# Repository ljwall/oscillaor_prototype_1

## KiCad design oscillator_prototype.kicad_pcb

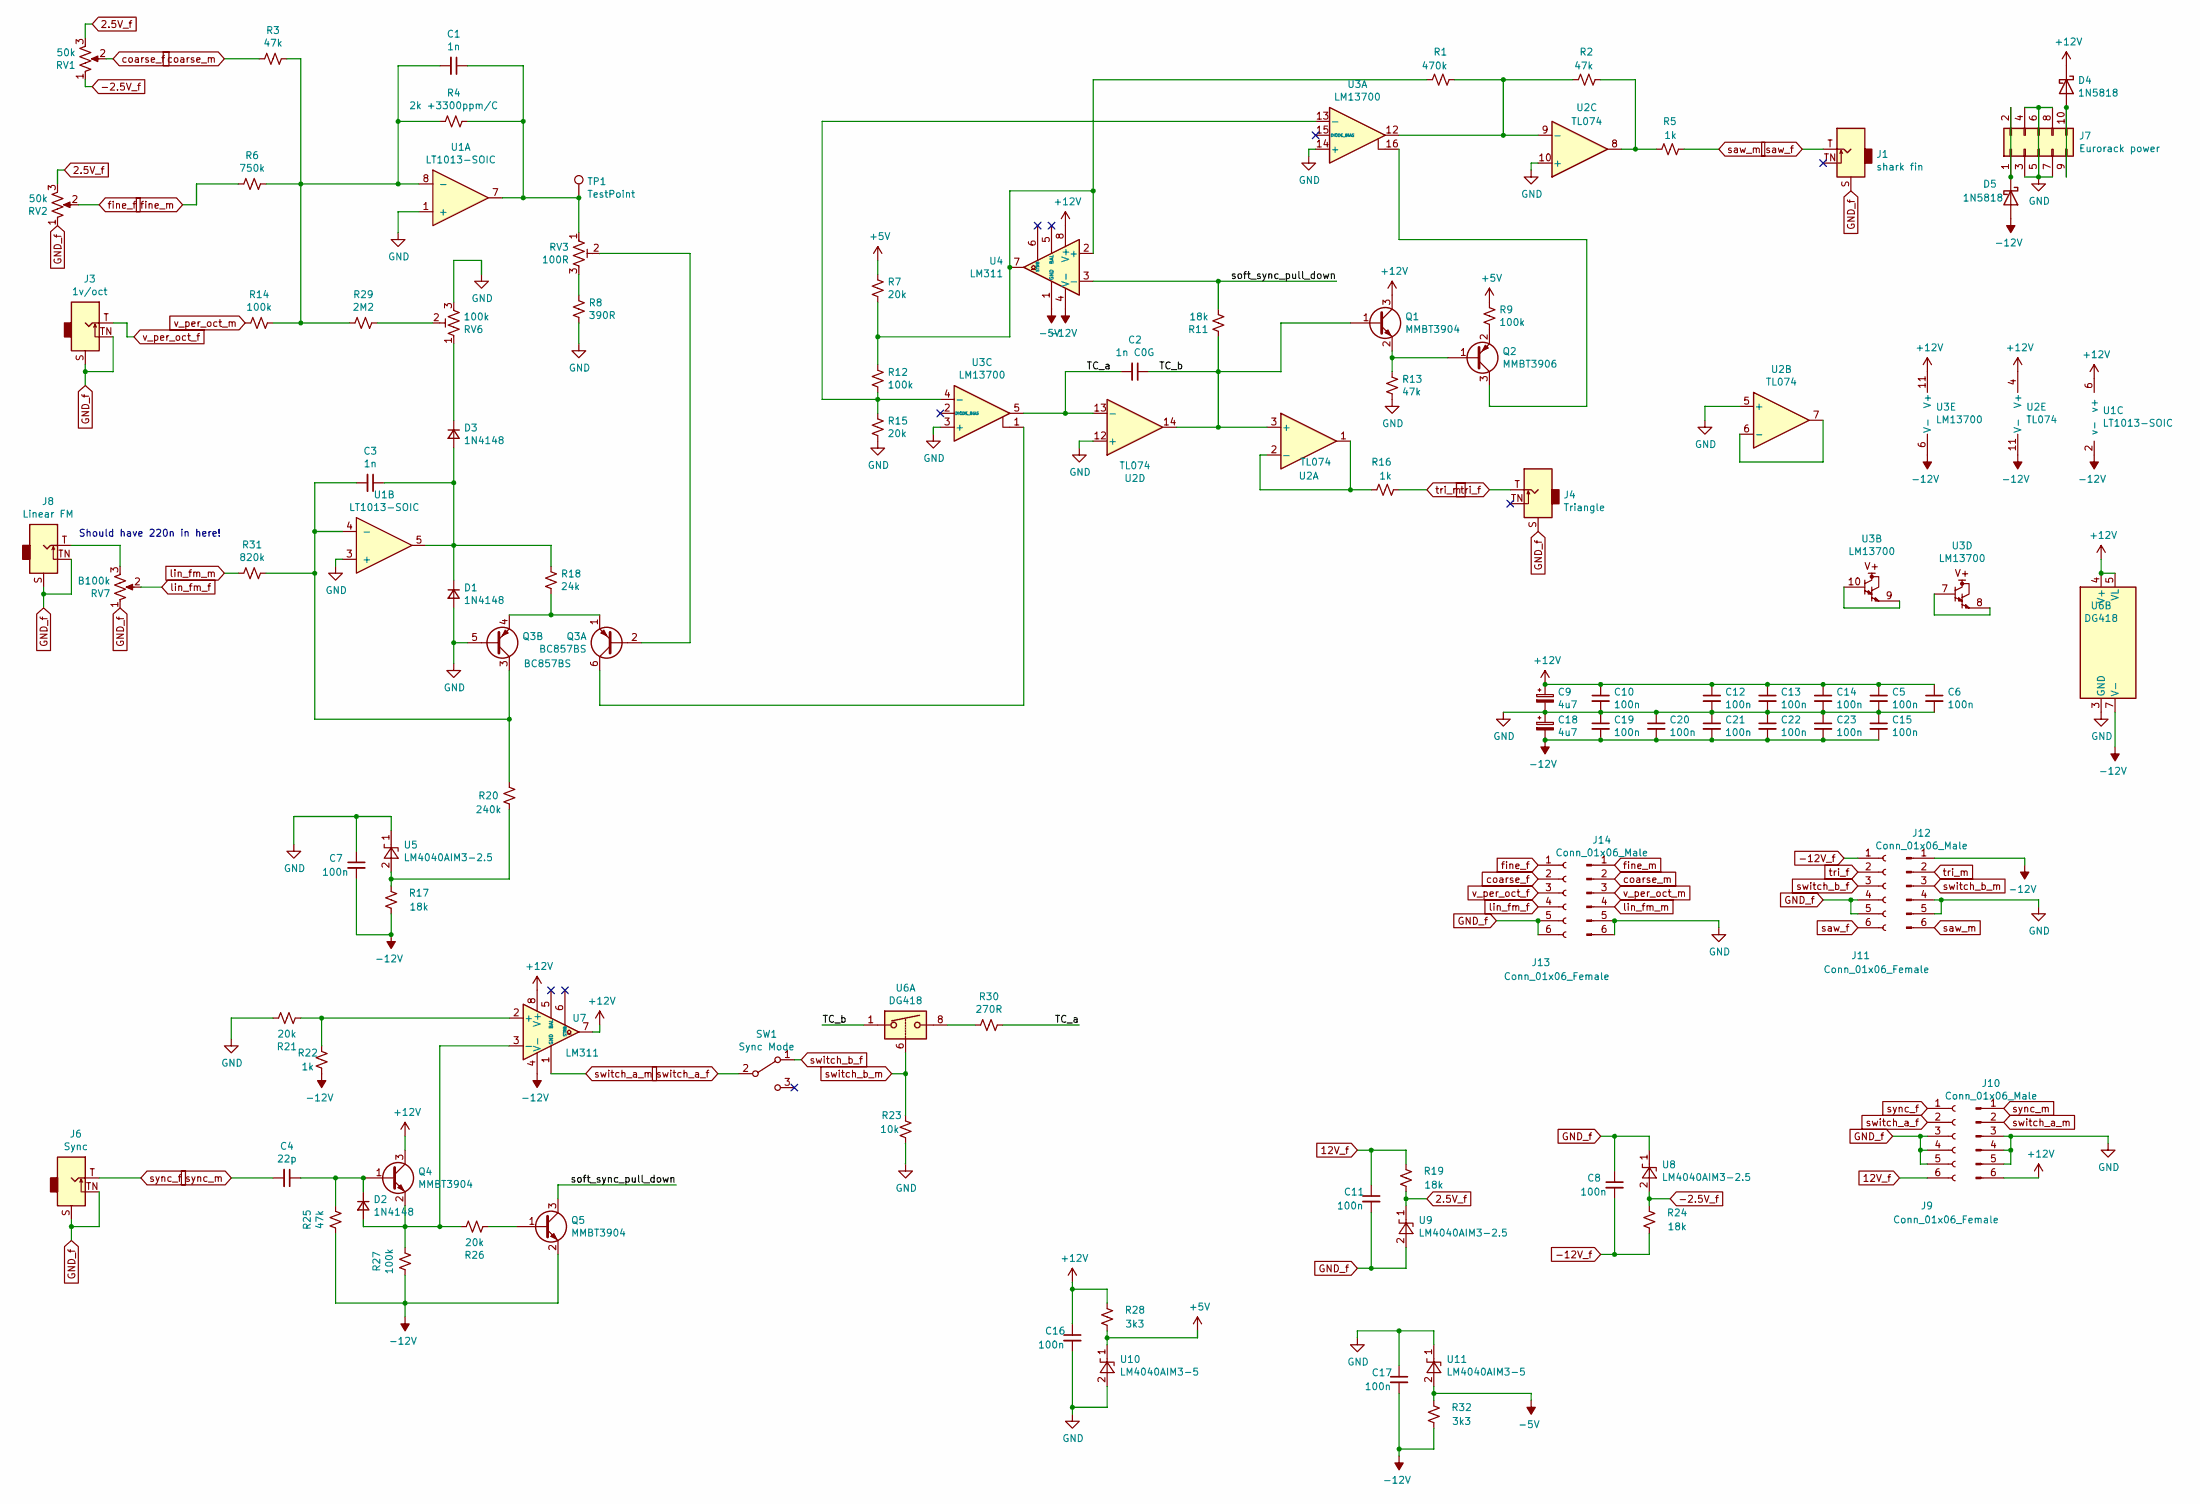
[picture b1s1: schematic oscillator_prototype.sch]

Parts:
C1, C3: 1n; C_0805_2012Metric_Pad1.18x1.45mm_HandSolder
C2: 1n C0G; C_0805_2012Metric_Pad1.18x1.45mm_HandSolder
C4: 22p; C_0805_2012Metric_Pad1.18x1.45mm_HandSolder
C5, C6, C7, C8, C10, C11, C12, C13, C14, C15, C16, C17, C19, C20, C21, C22, C23: 100n; C_0805_2012Metric_Pad1.18x1.45mm_HandSolder
C9, C18: 4u7; CP_Radial_D5.0mm_P2.00mm
D1, D2, D3: 1N4148; D_0805_2012Metric_Pad1.15x1.40mm_HandSolder
D4, D5: 1N5818; D_DO-41_SOD81_P10.16mm_Horizontal
J1: shark fin; Jack_3.5mm_QingPu_WQP-PJ398SM_Vertical_CircularHoles-transl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
J3: 1v/oct; Jack_3.5mm_QingPu_WQP-PJ398SM_Vertical_CircularHoles-transl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
J4: Triangle; Jack_3.5mm_QingPu_WQP-PJ398SM_Vertical_CircularHoles-transl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
J6: Sync; Jack_3.5mm_QingPu_WQP-PJ398SM_Vertical_CircularHoles-transl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
J7: Eurorack power; IDC-Header_2x05_P2.54mm_Horizontal
J8: Linear FM; Jack_3.5mm_QingPu_WQP-PJ398SM_Vertical_CircularHoles-transl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
J9, J11, J13: Conn_01x06_Female; PinHeader_1x06_P2.54mm_Vertical
J10, J12, J14: Conn_01x06_Male; PinHeader_1x06_P2.54mm_Vertical
Q1, Q4, Q5: MMBT3904; SOT-23
Q2: MMBT3906; SOT-23
Q3: BC857BS; SOT-363_SC-70-6
R1: 470k; R_0805_2012Metric_Pad1.20x1.40mm_HandSolder
R2, R3, R13, R25: 47k; R_0805_2012Metric_Pad1.20x1.40mm_HandSolder
R4: 2k +3300ppm/C; R_Axial_DIN0204_L3.6mm_D1.6mm_P5.08mm_Horizontal
R5, R16, R22: 1k; R_0805_2012Metric_Pad1.20x1.40mm_HandSolder
R6: 750k; R_0805_2012Metric_Pad1.20x1.40mm_HandSolder
R7, R15, R21, R26: 20k; R_0805_2012Metric_Pad1.20x1.40mm_HandSolder
R8: 390R; R_0805_2012Metric_Pad1.20x1.40mm_HandSolder
R9, R12, R14, R27: 100k; R_0805_2012Metric_Pad1.20x1.40mm_HandSolder
R11, R17, R19, R24: 18k; R_0805_2012Metric_Pad1.20x1.40mm_HandSolder
R18: 24k; R_0805_2012Metric_Pad1.20x1.40mm_HandSolder
R20: 240k; R_0805_2012Metric_Pad1.20x1.40mm_HandSolder
R23: 10k; R_0805_2012Metric_Pad1.20x1.40mm_HandSolder
R28, R32: 3k3; R_0805_2012Metric_Pad1.20x1.40mm_HandSolder
R29: 2M2; R_0805_2012Metric_Pad1.20x1.40mm_HandSolder
R30: 270R; R_0805_2012Metric_Pad1.20x1.40mm_HandSolder
R31: 820k; R_0805_2012Metric_Pad1.20x1.40mm_HandSolder
RV1, RV2: 50k; Potentiometer_Alpha_RD901F-40-00D_Single_Vertical-translated
RV3: 100R; Potentiometer_Bourns_3266X_Horizontal
RV6: 100k; Potentiometer_Bourns_3266X_Horizontal
RV7: B100k; Potentiometer_Alpha_RD901F-40-00D_Single_Vertical-translated
SW1: Sync Mode; Dailywell_sub-mini_toggle_SPDT
TP1: TestPoint; TestPoint_Pad_2.5x2.5mm
U1: LT1013-SOIC; SOIC-8_3.9x4.9mm_P1.27mm
U2: TL074; SOIC-14_3.9x8.7mm_P1.27mm
U3: LM13700; SOIC-16_3.9x9.9mm_P1.27mm
U4, U7: LM311; SOIC-8_3.9x4.9mm_P1.27mm
U5, U8, U9: LM4040AIM3-2.5; SOT-23
U6: DG418; SOIC-8_3.9x4.9mm_P1.27mm
U10, U11: LM4040AIM3-5; SOT-23

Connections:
2.5V_f: R19.2, RV1.3, RV2.3, U9.1 (K)
12V_f: C11.1, J9.6, R19.1
+5V: R7.2, R9.2, R28.2, U10.1 (K)
+12V: C5.1, C6.1, C9.1, C10.1, C12.1, C13.1, C14.1, C16.1, D4.1 (K), J10.6, Q1.3 (C), Q4.3 (C), R28.1, U1.6 (v+), U2.4 (V+), U3.11 (V+), U4.8 (V+), U6.4 (V+), U6.5 (VL), U7.7, U7.8 (V+)
-2.5V_f: R24.1, RV1.1, U8.2 (A)
-5V: R32.1, U4.1 (GND), U11.2 (A)
-12V: C7.2, C15.2, C17.2, C18.2, C19.2, C20.2, C21.2, C22.2, C23.2, D5.2 (A), J12.1, Q5.2 (E), R17.2, R22.2, R25.2, R27.2, R32.2, U1.2 (v-), U2.11 (V-), U3.6 (V-), U4.4 (V-), U6.7 (V-), U7.4 (V-)
-12V_f: C8.2, J11.1, R24.2
/TC_a: C2.2, R30.1, U2.13 (-), U3.5
/TC_b: C2.1, Q1.1 (B), R11.1, U2.3 (+), U2.14, U6.1
/soft_sync_pull_down: Q5.3 (C), R11.2, U4.3 (-)
GND: C5.2, C6.2, C7.1, C9.2, C10.2, C12.2, C13.2, C14.2, C15.1, C16.2, C17.1, C18.1, C19.1, C20.1, C21.1, C22.1, C23.1, D1.2 (A), J7.3, J7.4, J7.5, J7.6, J7.7, J7.8, J10.3, J10.4, J10.5, J12.4, J12.5, J14.5, J14.6, Q3.5 (B2), R8.1, R13.1, R15.1, R21.1, R23.2, RV6.3, U1.1 (+), U1.3 (+), U2.5 (+), U2.10 (+), U2.12 (+), U3.3 (+), U3.14 (+), U5.1 (K), U6.3 (GND), U10.2 (A), U11.1 (K)
GND_f: C8.1, C11.2, J1.S, J3.S, J3.TN, J4.S, J6.S, J6.TN, J8.S, J8.TN, J9.3, J9.4, J9.5, J11.4, J11.5, J13.5, J13.6, RV2.1, RV7.1, U8.1 (K), U9.2 (A)
unnamed: C1.1, R4.1, RV3.1, TP1.1, U1.7
unnamed: C1.2, R3.1, R4.2, R6.1, R14.1, R29.2, U1.8 (-)
unnamed: C3.1, D1.1 (K), D3.2 (A), R18.1, U1.5
unnamed: C3.2, Q3.3 (C2), R20.1, R31.1, U1.4 (-)
unnamed: C4.1, D2.1 (K), Q4.1 (B), R25.1
unnamed: D2.2 (A), Q4.2 (E), R26.1, R27.1, U7.3 (-)
unnamed: D3.1 (K), RV6.1
unnamed: D4.2 (A), J7.9, J7.10
unnamed: D5.1 (K), J7.1, J7.2
unnamed: J8.T, RV7.3
unnamed: Q1.2 (E), Q2.1 (B), R13.2
unnamed: Q2.2 (E), R9.1
unnamed: Q2.3 (C), U3.16
unnamed: Q3.1 (E1), Q3.4 (E2), R18.2
unnamed: Q3.2 (B1), RV3.2
unnamed: Q3.6 (C1), U3.1
unnamed: Q5.1 (B), R26.2
unnamed: R1.1, R7.1, R12.2, U4.2 (+), U4.7
unnamed: R1.2, R2.1, U2.9 (-), U3.12
unnamed: R2.2, R5.1, U2.8
unnamed: R8.2, RV3.3
unnamed: R12.1, R15.2, U3.4 (-), U3.13 (-)
unnamed: R16.1, U2.1, U2.2 (-)
unnamed: R17.1, R20.2, U5.2 (A)
unnamed: R21.2, R22.1, U7.2 (+)
unnamed: R29.1, RV6.2
unnamed: R30.2, U6.8
unnamed: U2.6 (-), U2.7
unnamed: U3.7, U3.8
unnamed: U3.9, U3.10
coarse_f: J13.2, RV1.2
coarse_m: J14.2, R3.2
fine_f: J13.1, RV2.2
fine_m: J14.1, R6.2
lin_fm_f: J13.4, RV7.2
lin_fm_m: J14.4, R31.2
saw_f: J1.T, J11.6
saw_m: J12.6, R5.2
switch_a_f: J9.2, SW1.2 (B)
switch_a_m: J10.2, U7.1 (GND)
switch_b_f: J11.3, SW1.1 (A)
switch_b_m: J12.3, R23.1, U6.6
sync_f: J6.T, J9.1
sync_m: C4.2, J10.1
tri_f: J4.T, J11.2
tri_m: J12.2, R16.2
v_per_oct_f: J3.T, J13.3
v_per_oct_m: J14.3, R14.2

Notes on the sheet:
Should have 220n in here!

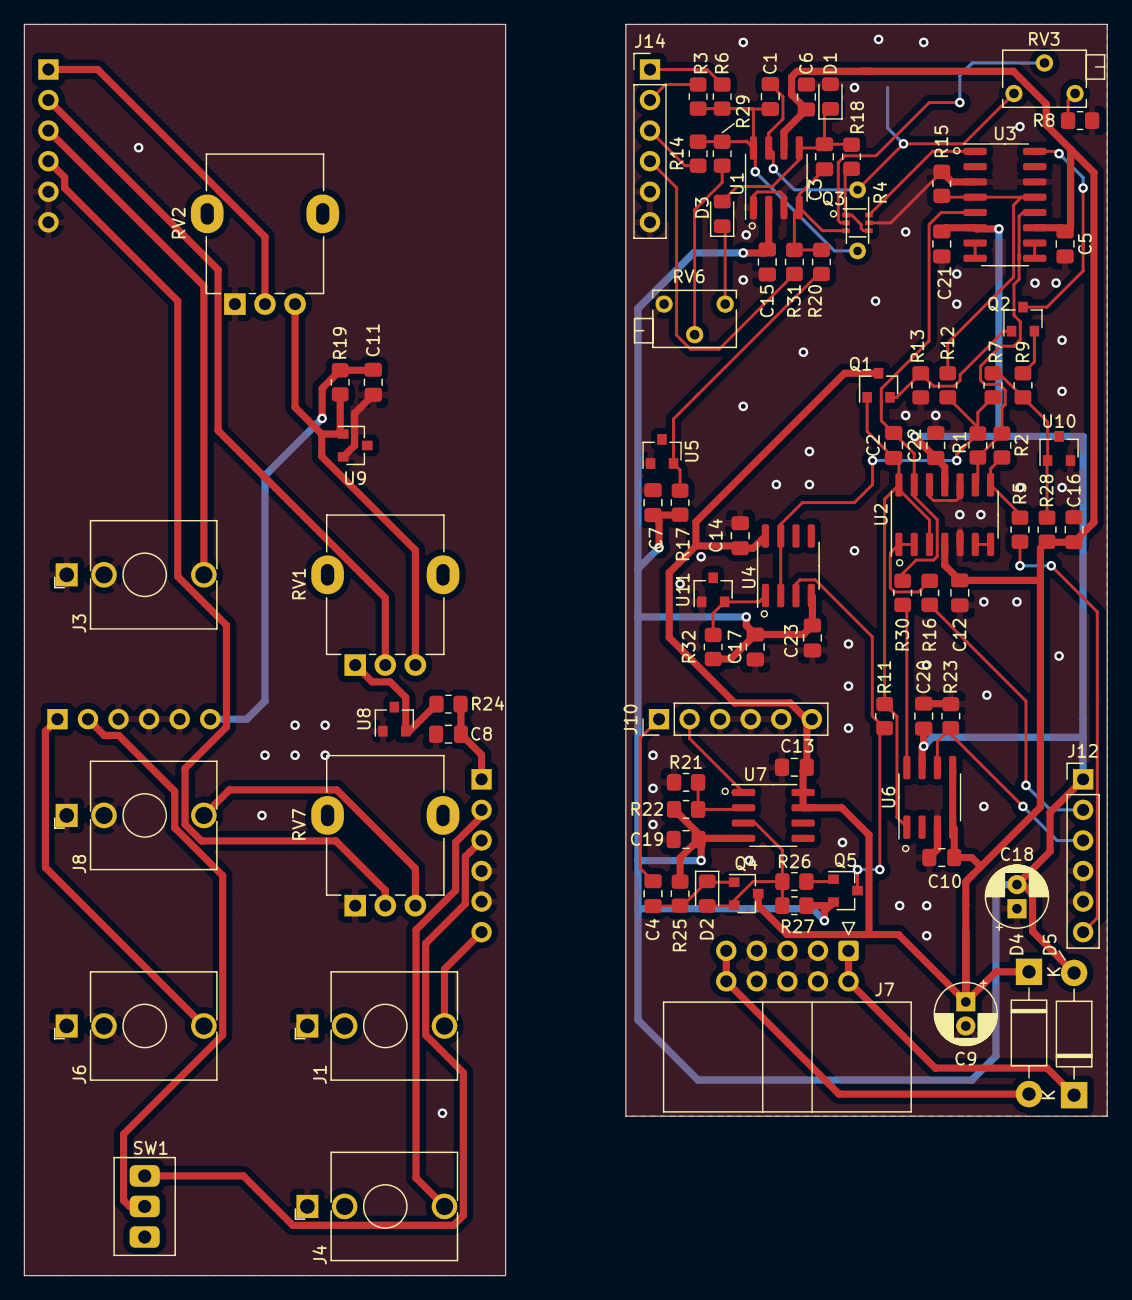
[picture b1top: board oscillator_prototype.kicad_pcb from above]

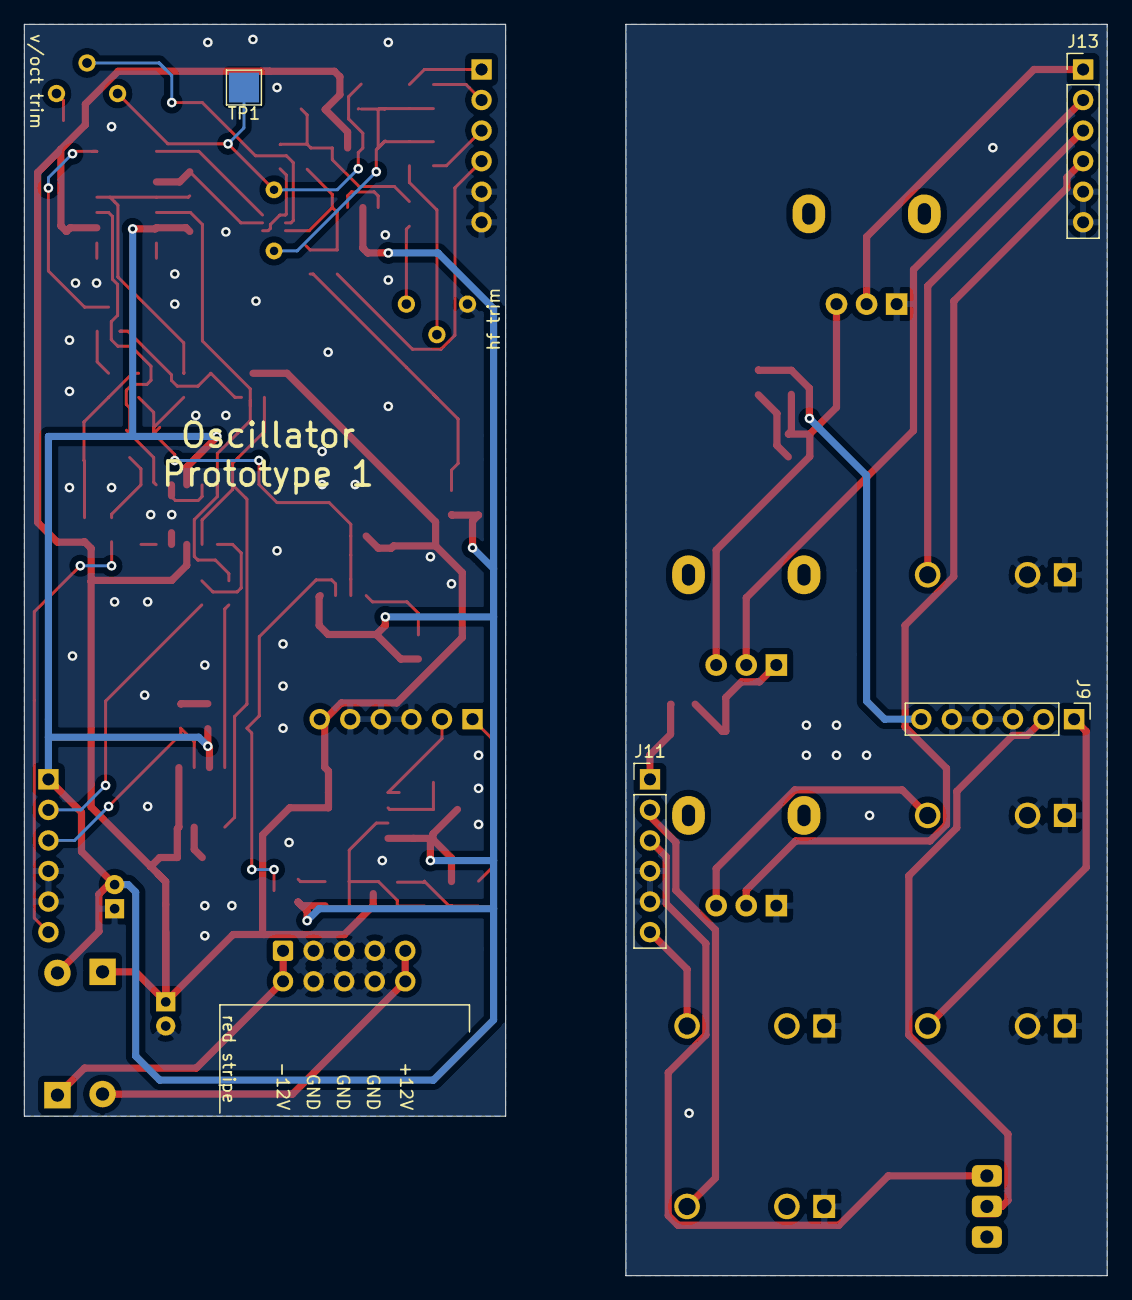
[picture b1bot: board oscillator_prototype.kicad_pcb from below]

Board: 2 copper layers, 40.0 x 90.8 mm, 94 parts (4 on the bottom side), 61 nets.

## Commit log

2020-11-08 Initial commit
    Schematic and through-hole footprint assingments for passives and SOIC
    (other SMD) for ICs and transistors
2020-11-08 Switch to SMT resistors/caps/diodes (mostly)
2020-11-08 Add initial panel files
2020-11-25 Complete layout
2020-12-05 Refactor layout and simplify circuit
2020-12-07 Add gerbers
2020-12-11 Add all missing component values to schematic
2020-12-17 Add BOM and panel
    minor change to BOM to reduce part count
2020-12-17 Highlight outputs on panel
2021-01-11 Correct -12v connection in saw shaper; add missing AC couple cap to linear FM input
